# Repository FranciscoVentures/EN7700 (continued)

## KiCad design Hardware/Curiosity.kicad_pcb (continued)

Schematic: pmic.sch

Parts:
C79: 2.2uF; SM0402; Rating 25V/20%; Mfg PN GRM155R61E225ME15D; Digi-Key_PN 490-10457-1-ND
C80: 47uF; SM0603; Rating 6.3V/20%; Mfg PN GRM188R60J476ME15D; Digi-Key_PN 490-13247-1-ND
C81, C82, C83, C96, C99: 4.7uF; SM0402; Rating 10V/20%; Mfg PN ZRB15XR61A475ME01D; Digi-Key_PN 490-10984-1-ND
C84, C85, C86, C87, C88, C89, C95: 10uF; SM0402; Rating 10V/20%; Mfg PN CL05A106MP8NUB8; Digi-Key_PN 1276-6830-1-ND
C90, C91, C92, C93, C97, C103, C104: 1uF; SM0201; Rating 10V/20%; Mfg PN CL03A105MP3ZSNH; Digi-Key_PN 1276-6816-1-ND
C94, C102: 0.1uF; SM0201; Rating 10V/20%; Mfg PN GRM033R61A104ME15D; Digi-Key_PN 490-5405-1-ND
C98: 0.47uF; SM0201; Rating 6.3V/20%; Mfg PN GRM033R60J474ME90D; Digi-Key_PN 490-10410-1-ND
D3: LED RED; LED_0603; Rating 20mA/2V; Mfg PN LS Q976-NR-1; Digi-Key_PN 475-2512-1-ND
D4: LED BLUE; LED_0603; Rating 5mA/2.85V; Mfg PN LB Q39G-L2OO-35-1; Digi-Key_PN 475-2816-1-ND
L1, L2, L3: 1uH; SM0603; Rating 1.7A/20%/135mOhm; Mfg PN LPWI160808H1R0T; Digi-Key_PN F12082CT-ND
R43, R46, R49: 100K; R_0201_0603Metric; Rating 50mW/1%; Mfg PN CRCW0201100KJNED; Digi-Key_PN 541-100KAGCT-ND
R44: 0R; R_0201_0603Metric; Rating 0.05W; Mfg PN CRCW02010000Z0ED; Digi-Key_PN 541-0.0AGCT-ND
R52: 68R; R_0201_0603Metric; Rating 50mW/1%; Mfg PN CRCW020168R0FNED; Digi-Key_PN 541-CRCW020168R0FNEDCT-ND
R53: 100R; R_0201_0603Metric; Rating 50mW/1%; Mfg PN CRCW0201100RFNED; Digi-Key_PN 541-100ABCT-ND
U18: MC34PF1510A6EP; SOT1369-4; Mfg PN MC34PF1510A6EP; Digi-Key_PN 568-14653-1-ND

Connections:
/PMIC/LICELL: C94.1, U18.31 (LICELL)
/PMIC/VCORE: C103.1, U18.24 (VCORE)
/PMIC/VDIG: C104.1, U18.23 (VDIG)
/PMIC/VSYS: C80.1, C81.1, C82.1, C83.1, C90.1, C91.1, C92.1, R46.1, U18.11 (VLDO3IN), U18.14 (SW3IN), U18.17 (SW2IN), U18.20 (VLDO2IN), U18.26 (SW1IN), U18.28 (VLDO1IN), U18.35 (VSYS1), U18.36 (VSYS2)
DCDC_3V3: C88.1, C89.1, C102.1, D3.2 (A), L3.2, U18.4 (VDDIO), U18.15 (SW3FB); also elsewhere on the board
DDR_1V35: C86.1, C87.1, C93.1, L2.2, U18.16 (SW2FB), U18.22 (VINREFDDR); also elsewhere on the board
DDR_VREF: C97.1, U18.21 (VREFDDR); also elsewhere on the board
GND: C79.2, C80.2, C81.2, C82.2, C83.2, C84.2, C85.2, C86.2, C87.2, C88.2, C89.2, C90.2, C91.2, C92.2, C93.2, C94.2, C95.2, C96.2, C97.2, C98.2, C99.2, C102.2, C103.2, C104.2, R52.2, R53.2, U18.5 (VDDOTP), U18.7 (STANDBY), U18.32 (GND), U18.40 (GND), U18.41 (EP); also elsewhere on the board
GPS_3V3: D4.2 (A), R44.2; also elsewhere on the board
I2C1_SCL: U18.3 (SCL); also elsewhere on the board
I2C1_SDA: U18.2 (SDA); also elsewhere on the board
LDO1_1V8: C99.1, U18.29 (VLDO1); also elsewhere on the board
LDO2_3V3: C95.1, U18.19 (VLDO2); also elsewhere on the board
unnamed: C96.1, R44.1, U18.12 (VLDO3)
unnamed: D3.1 (K), R52.1
unnamed: D4.1 (K), R53.1
unnamed: L1.1, U18.25 (SW1LX)
unnamed: L2.1, U18.18 (SW2LX)
unnamed: L3.1, U18.13 (SW3LX)
unnamed: R46.2, U18.8 (ONKEY)
unnamed: R49.2, U18.6 (PWRON)
PMIC_WDI: R43.1, U18.1 (WDI); also elsewhere on the board
VDD_ARM_SOC_IN: C84.1, C85.1, L1.2, U18.27 (SW1FB); also elsewhere on the board
VSNVS_3V: C98.1, R43.2, R49.1, U18.30 (VSNVS); also elsewhere on the board
VSYS_5V: C79.1, U18.37 (VIN); also elsewhere on the board

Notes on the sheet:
EPAD: Tie to the inner and external ground planes through vias to allow effective thermal dissipation. [1] pg 8
400 mA
300 mA
1 A
10 mA
Power rails
ULZ: NXP MC34PF1510A6EP
3V3 PWR RED LED
GPS_PWR
GPS PWR BLUE LED
EMMC HS200
VSYS = 3.7V
VDD_ARM_SOC_IN = 1.275V

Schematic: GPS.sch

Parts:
C106: 47pF; 0603; Rating 50V/5%; Mfg PN C0603C470J5GACTU; Digi-Key_PN 399-1056-1-ND
C107: 4.7uF; SM0402; Rating 10V/20%; Mfg PN ZRB15XR61A475ME01D; Digi-Key_PN 490-10984-1-ND
C108: 0.1uF; SM0201; Rating 10V/20%; Mfg PN GRM033R61A104ME15D; Digi-Key_PN 490-5405-1-ND
C109, C110: 18pF; SM0201; Rating 50V/5%; Mfg PN GRM0335C1H180JA01D; Digi-Key_PN 490-6117-1-ND
FB1: BLM18PG121SN1D; 0603; Mfg PN BLM18PG121SN1D; Digi-Key_PN 490-1037-1-ND
J3: CONUFL001-SMD-T; U.FL_Molex_MCRF_73412-0110_Vertical; Mouser Part Number 712-CONUFL001-SMD-T
L4: 2.2uH; INDC2016X180N; Rating 0806; Mfg PN LQM2MPN2R2NG0L; Digi-Key_PN 490-7786-1-ND
R45, R47: 0R; R_0201_0603Metric; Rating 0.05W; Mfg PN CRCW02010000Z0ED; Digi-Key_PN 541-0.0AGCT-ND
R54, R57, R58: 10K; R_0201_0603Metric; Rating 50mW/1%; Mfg PN CRCW020110K0JNED; Digi-Key_PN 541-10KAGCT-ND
R56: 100R; 0603; Rating 100mW/1%; Mfg PN RC0603FR-07100RL; Digi-Key_PN 311-100HRCT-ND
U21: ZOE-M8Q; ZOEM8B; Mfg PN ZOE-M8Q-0-10; Digi-Key_PN 672-ZOE-M8Q-0-10CT-ND
U22: TPD1E10B06; X1SON-2; Mfg PN TPD1E10B06DPYR; Digi-Key_PN 296-30406-1-ND
Y3: 32.768kHz; CM7V-T1A; Mfg PN CM7V-T1A-32.768KHZ-12.5PF-20PPM-TB-QA; Digi-Key_PN 2195-CM7V-T1A-32.768KHZ-12.5PF-20PPM-TB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

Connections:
GND: C106.1, C107.2, C108.2, C109.2, C110.2, J3.2 (GND_1), U21.A1 (GND_1), U21.A3 (GND_2), U21.A5 (GND_3), U21.A7 (GND_4), U21.A8 (GND_5), U21.A9 (GND_6), U21.B9 (GND_7), U21.C7 (GND_8), U21.C9 (GND_9), U21.D6 (GND_10), U21.D9 (GND_11), U21.E7 (GND_12), U21.F7 (GND_13), U21.G3 (GND_14), U21.G6 (GND_15), U21.G7 (GND_16), U21.J3 (GND_17), U21.J9 (GND_18), U22.1; also elsewhere on the board
GPS_3V3: C108.1, R54.1, R56.2, R57.2, R58.1, U21.H9 (V_BCKP), U21.J1 (VCC_3), U21.J2 (VCC_4); also elsewhere on the board
GPS_ANT: FB1.1, J3.1 (SIG), U21.A4 (RF_IN), U22.2
GPS_PIO14: R54.2, U21.F6 (PIO14); also elsewhere on the board
GPS_RESET: R58.2, U21.J6 (RESET_N); also elsewhere on the board
GPS_SAFEBOOT_N: R57.1, U21.C4 (SAFEBOOT_N); also elsewhere on the board
GPS_UART_RX: U21.J5 (TXD/SPI_MISO); also elsewhere on the board
GPS_UART_TX: U21.J4 (RXD/SPI_MOSI); also elsewhere on the board
I2C2_SCL: R47.1; also elsewhere on the board
I2C2_SDA: R45.1; also elsewhere on the board
unnamed: C106.2, FB1.2, R56.1
unnamed: C107.1, L4.2, U21.G1 (VCC_1)
unnamed: C109.1, U21.J7 (RTC_I), Y3.2
unnamed: C110.1, U21.J8 (RTC_O), Y3.1
unnamed: L4.1, U21.H1 (VCC_2)
unnamed: R45.2, U21.A2 (SDA_/_SPI_CS_N)
unnamed: R47.2, U21.B1 (SCL_/_SPI_CLK)

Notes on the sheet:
GPS I2C Address 0X42

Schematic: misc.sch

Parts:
C111, C114, C119, C120, C125: 0.22uF; SM0201; Rating 6.3V/20%; Mfg PN GRM033R60J224ME15D; Digi-Key_PN 490-10407-1-ND
C112, C123: 1uF; SM0201; Rating 10V/20%; Mfg PN CL03A105MP3ZSNH; Digi-Key_PN 1276-6816-1-ND
C113, C115, C118, C121: 0.1uF; SM0201; Rating 10V/20%; Mfg PN GRM033R61A104ME15D; Digi-Key_PN 490-5405-1-ND
C116: 10nF; SM0201; Rating 6.3V/10%; Mfg PN GRM033R70J103KA01D; Digi-Key_PN 490-1262-1-ND
C117: 2.2nF; C_0402_1005Metric; Rating 50V/5%; Mfg PN GRM155R71H222JA01J; Digi-Key_PN 490-6359-1-ND
C122: 10uF; C_0402_1005Metric; Rating 10V/20%; Mfg PN CL05A106MP8NUB8; Digi-Key_PN 1276-6830-1-ND
C124: 10uF; SM0402; Rating 10V/20%; Mfg PN CL05A106MP8NUB8; Digi-Key_PN 1276-6830-1-ND
D6: LED GREEN; LED_0603; Rating 5mA/2.85V; Mfg PN LT Q39G-Q1OO-25-1; Digi-Key_PN 475-3442-1-ND
D7: LED BLUE; SM0603_LED; Rating 5mA/2.85V; Mfg PN LB Q39G-L2OO-35-1; Digi-Key_PN 475-2816-1-ND
LED1: LED ORANGE; LED_0603; Rating 20mA/2V; Mfg PN LO Q976-PS-25-0-20-R18; Digi-Key_PN 475-2486-1-ND
LED2: LED BLUE; LED_0603; Rating 5mA/2.85V; Mfg PN LB Q39G-L2OO-35-1; Digi-Key_PN 475-2816-1-ND
LED3: LED CYAN; LED_0603; Rating 5mA/2.8V; Mfg PN APT1608VRCXF/A-5MAV; Digi-Key_PN 754-2180-1-ND
LED4: LED GREEN; LED_0603; Rating 5mA/2.85V; Mfg PN LT Q39G-Q1OO-25-1; Digi-Key_PN 475-3442-1-ND
LED5: LED RED; LED_0603; Rating 20mA/2V; Mfg PN LS Q976-NR-1; Digi-Key_PN 475-2512-1-ND
R59, R60, R68, R69, R70: 100R; R_0201_0603Metric; Rating 50mW/1%; Mfg PN CRCW0201100RFNED; Digi-Key_PN 541-100ABCT-ND
R61, R64, R65: 4.7K; R_0201_0603Metric; Rating 50mW/1%; Mfg PN CRCW02014K70JNED; Digi-Key_PN 541-4.7KAGCT-ND
R62: 10R; R_0201_0603Metric; Rating 50mW/1%; Mfg PN CRCW020110R0FNED; Digi-Key_PN 541-10.0ABCT-ND
R63: 10K; R_0201_0603Metric; Rating 50mW/1%; Mfg PN CRCW020110K0JNED; Digi-Key_PN 541-10KAGCT-ND
R66: 100K; R_0201_0603Metric; Rating 50mW/1%; Mfg PN CRCW0201100KJNED; Digi-Key_PN 541-100KAGCT-ND
R67, R71: 68R; R_0201_0603Metric; Rating 50mW/1%; Mfg PN CRCW020168R0FNED; Digi-Key_PN 541-CRCW020168R0FNEDCT-ND
U2: i.MX6ULZ; SOT1534-2; Mfg PN MCIMX6Z0DVM09AB; Digi-Key_PN 568-14726-ND
U23: MPU-6050_NRND; QFN-24-1EP_4x4mm; Mfg PN MPU-6050; Digi-Key_PN 1428-1007-1-ND
U24: MS860702BA01-50; TE_MS860702BA01-50; Mfg PN MS860702BA01-50; Digi-Key_PN 223-1701-1-ND
U25: VEML6030-GS15; VISHAY_VEML6030_2X2X0.87; Mfg PN VEML6030-GS15; Digi-Key_PN VEML6030-GS15CT-ND
U26: MMC5883MA; PQFN50P300X300X100-16N; Mfg PN MMC5883MA; Digi-Key_PN 1267-1072-1-ND

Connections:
A71CH_RESET: U2.A16 (ENET2_TX_DATA1); also elsewhere on the board
Amb_sensor_INT: R63.1, U2.M17 (GPIO1_IO05), U25.3; also elsewhere on the board
DCDC_3V3: C111.1, C114.1, C115.1, C116.1, C119.1, C120.1, C123.1, C125.1, LED1.2 (A), LED2.2 (A), LED3.2 (A), LED4.2 (A), LED5.2 (A), R61.2, R62.2, R63.2, R64.1, R65.1, U2.C4 (NVCC_SD1), U2.F4 (NVCC_CSI), U2.F13 (NVCC_ENET), U2.J13 (NVCC_GPIO), U23.8 (VLOGIC), U23.13 (VDD), U24.1 (VDD), U26.2 (VDD), U26.13 (VDDIO); also elsewhere on the board
GND: C111.2, C112.2, C113.2, C114.2, C115.2, C116.2, C117.2, C118.2, C119.2, C120.2, C121.2, C122.2, C123.2, C124.2, C125.2, R66.2, U23.1 (CLKIN), U23.9 (AD0), U23.11 (FSYNC), U23.18 (GND), U24.3 (GND), U25.1, U26.9 (GND), U26.11 (GND); also elsewhere on the board
GPS_PIO14: U2.B1 (SD1_DATA2), U2.D16 (ENET2_RX_ER); also elsewhere on the board
GPS_RESET: U2.B2 (SD1_DATA1), U2.C16 (ENET2_RX_DATA1); also elsewhere on the board
GPS_SAFEBOOT_N: U2.C2 (SD1_CMD), U2.D17 (ENET2_TX_CLK); also elsewhere on the board
I2C1_SCL: R64.2, U2.L14 (GPIO1_IO02); also elsewhere on the board
I2C1_SDA: R65.2, U2.L17 (GPIO1_IO03); also elsewhere on the board
I2C2_SCL: U23.23 (SCL/SCLK), U24.8 (SCL), U25.5, U26.1 (SCL); also elsewhere on the board
I2C2_SDA: U23.24 (SDA), U24.7 (SDA), U25.2, U26.16 (SDA); also elsewhere on the board
ICS43434_SCK: U2.E1 (CSI_DATA03); also elsewhere on the board
ICS43434_SD: U2.D2 (CSI_DATA06); also elsewhere on the board
ICS43434_WS: U2.E2 (CSI_DATA02); also elsewhere on the board
LDO2_3V3: C112.1, C113.1, D6.2 (A), D7.2 (A), U2.L13 (VDDA_ADC_3P3), U2.M13 (ADC_VREFH); also elsewhere on the board
MPU6K_INT: R61.1, U2.L15 (GPIO1_IO01), U23.12 (INT); also elsewhere on the board
unnamed: C117.1, U23.20 (CPOUT)
unnamed: C118.1, U23.10 (REGOUT)
unnamed: C121.1, C122.1, R62.1, U25.4, U25.6
unnamed: C124.1, U26.10 (CAP)
unnamed: D6.1 (K), R59.1
unnamed: D7.1 (K), R60.1
unnamed: LED1.1 (K), R67.1
unnamed: LED2.1 (K), R68.1
unnamed: LED3.1 (K), R69.1
unnamed: LED4.1 (K), R70.1
unnamed: LED5.1 (K), R71.1
unnamed 179: R59.2, U2.E4 (CSI_DATA00); also elsewhere on the board
unnamed 180: R60.2, U2.E3 (CSI_DATA01); also elsewhere on the board
unnamed 181: U2.A2 (SD1_DATA3); also elsewhere on the board
unnamed 185: U2.A15 (ENET2_TX_DATA0); also elsewhere on the board
unnamed 186: U2.B3 (SD1_DATA0); also elsewhere on the board
unnamed 189: U2.B15 (ENET2_TX_EN); also elsewhere on the board
unnamed 190: U2.C1 (SD1_CLK); also elsewhere on the board
unnamed 193: U2.D1 (CSI_DATA07); also elsewhere on the board
unnamed 194: U2.D3 (CSI_DATA05); also elsewhere on the board
unnamed 195: U2.D4 (CSI_DATA04); also elsewhere on the board
unnamed 198: U2.D15 (ENET1_RX_ER); also elsewhere on the board
unnamed 199: U2.E5 (CSI_PIXCLK); also elsewhere on the board
unnamed 202: U2.E14 (ENET1_TX_DATA1); also elsewhere on the board
unnamed 203: U2.E15 (ENET1_TX_DATA0); also elsewhere on the board
unnamed 204: U2.E16 (ENET1_RX_EN); also elsewhere on the board
unnamed 205: U2.E17 (ENET1_RX_DATA1); also elsewhere on the board
unnamed 207: U2.F2 (CSI_VSYNC); also elsewhere on the board
unnamed 208: U2.F3 (CSI_HSYNC); also elsewhere on the board
unnamed 209: U2.F5 (CSI_MCLK); also elsewhere on the board
unnamed 210: U2.F14 (ENET1_TX_CLK); also elsewhere on the board
unnamed 211: U2.F16 (ENET1_RX_DATA0); also elsewhere on the board
PMIC_WDI: U2.F15 (ENET1_TX_EN); also elsewhere on the board
SE1_LED: R67.2, U2.M15 (GPIO1_IO09); also elsewhere on the board
SE2_LED: R68.2, U2.N17 (GPIO1_IO08); also elsewhere on the board
SE3_LED: R69.2, U2.L16 (GPIO1_IO07); also elsewhere on the board
SE4_LED: R70.2, U2.K17 (GPIO1_IO06); also elsewhere on the board
SE5_LED: R71.2, U2.M16 (GPIO1_IO04); also elsewhere on the board
SLS32A_RESET: U2.C17 (ENET2_RX_DATA0); also elsewhere on the board
USB1_INT_B: U2.K13 (GPIO1_IO00); also elsewhere on the board
eCompass_INT: R66.1, U2.B17 (ENET2_RX_EN), U26.15 (INT); also elsewhere on the board

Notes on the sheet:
ADC_VREFH: tied to VDDA_ADC_3P3 [1] pg 18
VDDA_ADC_3P3 must be powered even if the ADC is not used. [1] pg 18
I2C1_SCL [ALT0]
I2C1_SDA [ALT0]
GPIO1_IO9 [ALT5]
GPIO1_IO6 [ALT5]
GPIO1_IO4 [ALT5]
I2C1 ADDRESSES (8bit address / 7 bit address) 0x10 / 0x08: PMIC (400 kHz) 0xC0 / 0x60: ATECC608A Microchip SECURE ELEMENT (1 MHz) 0x92 / 0x49: A71CH NXP SECURE ELEMENT (400 kHz) 0xC2 / 0x61: TUSB320 USB1 (Type-C plug) (400 kHz) 0x30 / 0x : SLS32AIA010MH OPTIGA SECURE ELEMENT (400kHz) 0x50 / 0x : A1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
GPIO1_IO0 [ALT5]
ENET1_TX_EN (ULZ: KPP_COL2) -> WDOG2_WDOG_RST_B_DEB [ALT8]
CSI_DATA00 (ULZ: SD2_DATA0) -> GPIO4_IO21 [ALT5]
CSI_DATA01 (ULZ: SD2_DATA1) -> GPIO4_IO22 [ALT5]
ULZ: VDD_HIGH_IN
Secure Elements LEDS
Pressure, Humidity & Temp Sensors
I2C Adress: Pressure & Tempreature: 0x76 Relative Humidity: 0x40
High Accuracy Ambient Light Sensor
I2C Adress: 0x48
GPIO1_IO5 [ALT5]-Ambient Sensor Interrupt
GPIO1_IO7 [ALT5]
GPIO1_IO8 [ALT5]
I2C Adress: 0x68
GPIO1_IO1 [ALT5]
Accelerometer, Gyroscope, 6 Axis Sensor
RX_SYNC -> CSI_DATA02 -> GPIO4_IO23
RX_BCLK -> CSI_DATA03 -> GPIO4_IO24
RX_DATA -> CSI_DATA06 -> GPIO4_IO27
GPIO2_IO8
GPIO2_IO9
GPIO2_IO15
e-Compass
I2C Adress: 0x30
GPIO2_IO14
I2C2 ADDRESSES (8bit address / 7 bit address) 0x76 / 0xXX: Pressure & Tempreature (400KHz) 0x40 / 0xXX: Relative Humidity (400KHz) 0x48 / 0xXX: Ambient Light Sensor (400KHz) 0x68 / 0xXX: Acc Gyro 6 Axis Sensor (400KHz) 0x30 / 0xXX: eCompass (400KHz) 0x42 / 0x21: GPS ZOE-M8Q-0-10 (400 kHz) 0x52 / 0x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
GPIO2_IO10

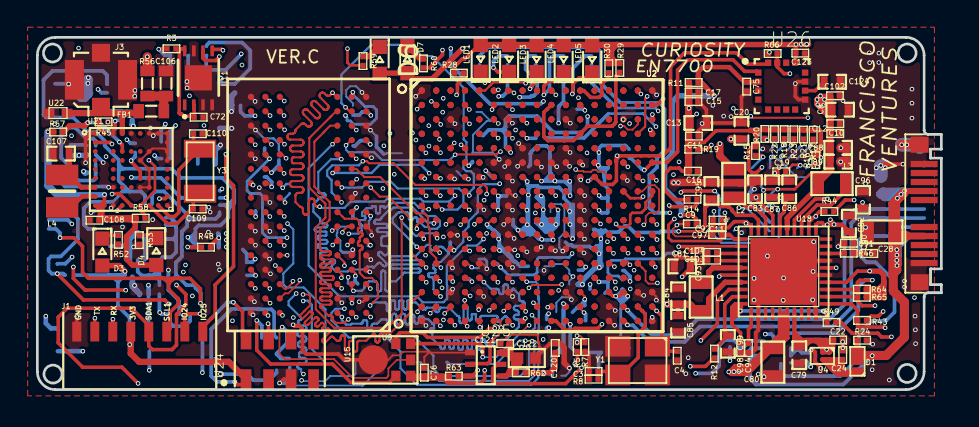
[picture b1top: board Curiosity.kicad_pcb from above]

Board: 8 copper layers, 50.2 x 19.6 mm, 246 parts (0 on the bottom side), 257 nets.

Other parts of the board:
U2#2: i.MX6ULZ; SOT1534-2

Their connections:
/Boot/BT_CFG1[0]: U2#2.B9; also elsewhere on the board
/Boot/BT_CFG1[1]: U2#2.A9; also elsewhere on the board
/Boot/BT_CFG1[2]: U2#2.E10; also elsewhere on the board
/Boot/BT_CFG1[3]: U2#2.D10; also elsewhere on the board
/Boot/BT_CFG1[4]: U2#2.C10; also elsewhere on the board
/Boot/BT_CFG1[5]: U2#2.B10, U2#2.D12; also elsewhere on the board
/Boot/BT_CFG1[6]: U2#2.A10; also elsewhere on the board
/Boot/BT_CFG1[7]: U2#2.D11; also elsewhere on the board
/Boot/BT_CFG2[0]: U2#2.B11; also elsewhere on the board
/Boot/BT_CFG2[1]: U2#2.A11; also elsewhere on the board
/Boot/BT_CFG2[2]: U2#2.E12; also elsewhere on the board
/Boot/BT_CFG2[4]: U2#2.C12; also elsewhere on the board
/Boot/BT_CFG2[5]: U2#2.B12; also elsewhere on the board
/Boot/BT_CFG2[6]: U2#2.A12; also elsewhere on the board
/Boot/BT_CFG2[7]: U2#2.D13; also elsewhere on the board
/Boot/BT_CFG4[0]: U2#2.C13; also elsewhere on the board
/Boot/BT_CFG4[1]: U2#2.B13; also elsewhere on the board
/Boot/BT_CFG4[2]: U2#2.A13; also elsewhere on the board
/Boot/BT_CFG4[3]: U2#2.D14; also elsewhere on the board
/Boot/BT_CFG4[4]: U2#2.C14; also elsewhere on the board
/Boot/BT_CFG4[5]: U2#2.B14; also elsewhere on the board
/Boot/BT_CFG4[6]: U2#2.A14; also elsewhere on the board
/Boot/BT_CFG4[7]: U2#2.B16; also elsewhere on the board
/Crystals/BOOT_MODE0: U2#2.T10; also elsewhere on the board
/Crystals/BOOT_MODE1: U2#2.U10; also elsewhere on the board
/Crystals/JTAG_MOD: U2#2.P15; also elsewhere on the board
/Crystals/JTAG_TCK: U2#2.M14; also elsewhere on the board
/Crystals/JTAG_TDI: U2#2.N16; also elsewhere on the board
/Crystals/JTAG_TDO: U2#2.N15; also elsewhere on the board
/Crystals/JTAG_TMS: U2#2.P14; also elsewhere on the board
/Crystals/JTAG_nSRST: U2#2.P8; also elsewhere on the board
/Crystals/JTAG_nTRST: U2#2.N14; also elsewhere on the board
/Crystals/RTC_XTALI: U2#2.T11; also elsewhere on the board
/Crystals/RTC_XTALO: U2#2.U11; also elsewhere on the board
/Crystals/XTALI: U2#2.T16; also elsewhere on the board
/Crystals/XTALO: U2#2.T17; also elsewhere on the board
/DDR/DRAM_A0: U2#2.L5; also elsewhere on the board
/DDR/DRAM_A1: U2#2.H2; also elsewhere on the board
/DDR/DRAM_A2: U2#2.K1; also elsewhere on the board
/DDR/DRAM_A3: U2#2.M2; also elsewhere on the board
/DDR/DRAM_A4: U2#2.K4; also elsewhere on the board
/DDR/DRAM_A5: U2#2.L1; also elsewhere on the board
/DDR/DRAM_A6: U2#2.G2; also elsewhere on the board
/DDR/DRAM_A7: U2#2.H4; also elsewhere on the board
/DDR/DRAM_A8: U2#2.J4; also elsewhere on the board
/DDR/DRAM_A9: U2#2.L2; also elsewhere on the board
/DDR/DRAM_A10: U2#2.M4; also elsewhere on the board
/DDR/DRAM_A11: U2#2.K3; also elsewhere on the board
/DDR/DRAM_A12: U2#2.L4; also elsewhere on the board
/DDR/DRAM_A13: U2#2.H3; also elsewhere on the board
/DDR/DRAM_A14: U2#2.G1; also elsewhere on the board
/DDR/DRAM_A15: U2#2.K5; also elsewhere on the board
/DDR/DRAM_CAS_B: U2#2.J2; also elsewhere on the board
/DDR/DRAM_CS0_B: U2#2.N2; also elsewhere on the board
/DDR/DRAM_D0: U2#2.T4; also elsewhere on the board
/DDR/DRAM_D1: U2#2.U6; also elsewhere on the board
/DDR/DRAM_D2: U2#2.T6; also elsewhere on the board
/DDR/DRAM_D3: U2#2.U7; also elsewhere on the board
/DDR/DRAM_D4: U2#2.U8; also elsewhere on the board
/DDR/DRAM_D5: U2#2.T8; also elsewhere on the board
/DDR/DRAM_D6: U2#2.T5; also elsewhere on the board
/DDR/DRAM_D7: U2#2.U4; also elsewhere on the board
/DDR/DRAM_D8: U2#2.U2; also elsewhere on the board
/DDR/DRAM_D9: U2#2.U3; also elsewhere on the board
/DDR/DRAM_D10: U2#2.U5; also elsewhere on the board
/DDR/DRAM_D11: U2#2.R4; also elsewhere on the board
/DDR/DRAM_D12: U2#2.P5; also elsewhere on the board
/DDR/DRAM_D13: U2#2.P3; also elsewhere on the board
/DDR/DRAM_D14: U2#2.R2; also elsewhere on the board
/DDR/DRAM_D15: U2#2.R1; also elsewhere on the board
/DDR/DRAM_DQM0: U2#2.T7; also elsewhere on the board
/DDR/DRAM_DQM1: U2#2.T3; also elsewhere on the board
/DDR/DRAM_RAS_B: U2#2.M5; also elsewhere on the board
/DDR/DRAM_RESET_B: U2#2.G4; also elsewhere on the board
/DDR/DRAM_SDBA0: U2#2.M1; also elsewhere on the board
/DDR/DRAM_SDBA1: U2#2.H1; also elsewhere on the board
/DDR/DRAM_SDBA2: U2#2.K2; also elsewhere on the board
/DDR/DRAM_SDCKE0: U2#2.M3; also elsewhere on the board
/DDR/DRAM_SDCLK0_N: U2#2.P2; also elsewhere on the board
/DDR/DRAM_SDCLK0_P: U2#2.P1; also elsewhere on the board
/DDR/DRAM_SDODT0: U2#2.N1; also elsewhere on the board
/DDR/DRAM_SDQS0_N: U2#2.P7; also elsewhere on the board
/DDR/DRAM_SDQS0_P: U2#2.P6; also elsewhere on the board
/DDR/DRAM_SDQS1_N: U2#2.T2; also elsewhere on the board
/DDR/DRAM_SDQS1_P: U2#2.T1; also elsewhere on the board
/DDR/DRAM_WE_B: U2#2.J1; also elsewhere on the board
/DDR/DRAM_ZQPAD: U2#2.N4; also elsewhere on the board
/Power/NVCC_PLL_OUT: U2#2.P13; also elsewhere on the board
/Power/VDD_ARM_CAP: U2#2.G9, U2#2.G10, U2#2.G11, U2#2.H11; also elsewhere on the board
/Power/VDD_SNVS_CAP: U2#2.N12; also elsewhere on the board
/Power/VDD_SOC_CAP: U2#2.G8, U2#2.H8, U2#2.J8, U2#2.J11, U2#2.K8, U2#2.K11, U2#2.L8, U2#2.L9, U2#2.L10, U2#2.L11; also elsewhere on the board
/USB/USB1_DN: U2#2.T15; also elsewhere on the board
/USB/USB1_DP: U2#2.U15; also elsewhere on the board
/USB/VDD_USB_CAP: U2#2.R12; also elsewhere on the board
/eMMC/SD2_CLK_R: U2#2.D8; also elsewhere on the board
/eMMC/SD2_CMD: U2#2.C8; also elsewhere on the board
/eMMC/SD2_DATA0: U2#2.D7; also elsewhere on the board
/eMMC/SD2_DATA1: U2#2.B7; also elsewhere on the board
/eMMC/SD2_DATA2: U2#2.A7; also elsewhere on the board
/eMMC/SD2_DATA3: U2#2.D6; also elsewhere on the board
/eMMC/SD2_DATA4: U2#2.C6; also elsewhere on the board
/eMMC/SD2_DATA5: U2#2.B6; also elsewhere on the board
/eMMC/SD2_DATA6: U2#2.A6; also elsewhere on the board
/eMMC/SD2_DATA7: U2#2.A5; also elsewhere on the board
/eMMC/SD2_RESET_B: U2#2.B4; also elsewhere on the board
A71CH_RESET: U2#2.A16; also elsewhere on the board
Amb_sensor_INT: U2#2.M17; also elsewhere on the board
DCDC_3V3: U2#2.C4, U2#2.E13, U2#2.F4, U2#2.F13, U2#2.H13, U2#2.J13; also elsewhere on the board
DDR_1V35: U2#2.G6, U2#2.H6, U2#2.J6, U2#2.K6, U2#2.L6, U2#2.M6; also elsewhere on the board
DDR_VREF: U2#2.P4; also elsewhere on the board
GND: U2#2.A1, U2#2.A17, U2#2.C3, U2#2.C7, U2#2.C11, U2#2.C15, U2#2.E8, U2#2.E11, U2#2.F6, U2#2.F7, U2#2.F8, U2#2.F9, U2#2.F10, U2#2.F11, U2#2.F12, U2#2.G3, U2#2.G5, U2#2.G7, U2#2.G12, U2#2.G15, U2#2.H7, U2#2.H12, U2#2.J5, U2#2.J7, U2#2.J12, U2#2.K7, U2#2.K12, U2#2.L3, U2#2.L7, U2#2.L12, U2#2.M7, U2#2.M8, U2#2.M9, U2#2.M10, U2#2.M11, U2#2.M12, U2#2.N3, U2#2.N5, U2#2.N7, U2#2.R3, U2#2.R5, U2#2.R7, U2#2.R11, U2#2.R16, U2#2.R17, U2#2.T14, U2#2.U1, U2#2.U14, U2#2.U17; also elsewhere on the board
GPIO1_IO25: U2#2.H15; also elsewhere on the board
GPIO1_IO27: U2#2.G14; also elsewhere on the board
GPS_PIO14: U2#2.B1, U2#2.D16; also elsewhere on the board
GPS_RESET: U2#2.B2, U2#2.C16; also elsewhere on the board
GPS_SAFEBOOT_N: U2#2.C2, U2#2.D17; also elsewhere on the board
GPS_UART_RX: U2#2.H16; also elsewhere on the board
GPS_UART_TX: U2#2.H17; also elsewhere on the board
I2C1_SCL: U2#2.L14; also elsewhere on the board
I2C1_SDA: U2#2.L17; also elsewhere on the board
I2C2_SCL: U2#2.F17; also elsewhere on the board
I2C2_SDA: U2#2.G13; also elsewhere on the board
ICS43434_SCK: U2#2.E1; also elsewhere on the board
ICS43434_SD: U2#2.D2; also elsewhere on the board
ICS43434_WS: U2#2.E2; also elsewhere on the board
LDO2_3V3: U2#2.L13, U2#2.M13, U2#2.N13, U2#2.P12; also elsewhere on the board
MPU6K_INT: U2#2.L15; also elsewhere on the board
NVCC_NAND: U2#2.E7; also elsewhere on the board
unnamed 179: U2#2.E4; also elsewhere on the board
unnamed 180: U2#2.E3; also elsewhere on the board
unnamed 181: U2#2.A2; also elsewhere on the board
unnamed 182: U2#2.A3; also elsewhere on the board
unnamed 183: U2#2.A4; also elsewhere on the board
unnamed 184: U2#2.A8; also elsewhere on the board
unnamed 185: U2#2.A15; also elsewhere on the board
unnamed 186: U2#2.B3; also elsewhere on the board
unnamed 187: U2#2.B5; also elsewhere on the board
unnamed 188: U2#2.B8; also elsewhere on the board
unnamed 189: U2#2.B15; also elsewhere on the board
unnamed 190: U2#2.C1; also elsewhere on the board
unnamed 191: U2#2.C5; also elsewhere on the board
unnamed 192: U2#2.C9; also elsewhere on the board
unnamed 193: U2#2.D1; also elsewhere on the board
unnamed 194: U2#2.D3; also elsewhere on the board
unnamed 195: U2#2.D4; also elsewhere on the board
unnamed 196: U2#2.D5; also elsewhere on the board
unnamed 197: U2#2.D9; also elsewhere on the board
unnamed 198: U2#2.D15; also elsewhere on the board
unnamed 199: U2#2.E5; also elsewhere on the board
unnamed 200: U2#2.E6; also elsewhere on the board
unnamed 201: U2#2.E9; also elsewhere on the board
unnamed 202: U2#2.E14; also elsewhere on the board
unnamed 203: U2#2.E15; also elsewhere on the board
unnamed 204: U2#2.E16; also elsewhere on the board
unnamed 205: U2#2.E17; also elsewhere on the board
unnamed 206: U2#2.F1; also elsewhere on the board
unnamed 207: U2#2.F2; also elsewhere on the board
unnamed 208: U2#2.F3; also elsewhere on the board
unnamed 209: U2#2.F5; also elsewhere on the board
unnamed 210: U2#2.F14; also elsewhere on the board
unnamed 211: U2#2.F16; also elsewhere on the board
unnamed 212: U2#2.H5; also elsewhere on the board
unnamed 213: U2#2.H14; also elsewhere on the board
unnamed 214: U2#2.J3; also elsewhere on the board
unnamed 215: U2#2.J14; also elsewhere on the board
unnamed 216: U2#2.J15; also elsewhere on the board
unnamed 217: U2#2.J16; also elsewhere on the board
unnamed 218: U2#2.J17; also elsewhere on the board
unnamed 219: U2#2.K14; also elsewhere on the board
unnamed 220: U2#2.K15; also elsewhere on the board
unnamed 221: U2#2.K16; also elsewhere on the board
unnamed 222: U2#2.N8; also elsewhere on the board
unnamed 223: U2#2.N9; also elsewhere on the board
unnamed 224: U2#2.N10; also elsewhere on the board
unnamed 225: U2#2.N11; also elsewhere on the board
unnamed 226: U2#2.P9; also elsewhere on the board
unnamed 227: U2#2.P10; also elsewhere on the board
unnamed 228: U2#2.P11; also elsewhere on the board
unnamed 229: U2#2.P16; also elsewhere on the board
unnamed 230: U2#2.P17; also elsewhere on the board
unnamed 231: U2#2.R6; also elsewhere on the board
unnamed 232: U2#2.R8; also elsewhere on the board
unnamed 233: U2#2.R9; also elsewhere on the board
unnamed 234: U2#2.R10; also elsewhere on the board
unnamed 235: U2#2.R13; also elsewhere on the board
unnamed 236: U2#2.T9; also elsewhere on the board
unnamed 237: U2#2.T13; also elsewhere on the board
unnamed 238: U2#2.U9; also elsewhere on the board
unnamed 239: U2#2.U12; also elsewhere on the board
unnamed 240: U2#2.U13; also elsewhere on the board
unnamed 241: U2#2.U16; also elsewhere on the board
PMIC_WDI: U2#2.F15; also elsewhere on the board
SE1_LED: U2#2.M15; also elsewhere on the board
SE2_LED: U2#2.N17; also elsewhere on the board
SE3_LED: U2#2.L16; also elsewhere on the board
SE4_LED: U2#2.K17; also elsewhere on the board
SE5_LED: U2#2.M16; also elsewhere on the board
SLS32A_RESET: U2#2.C17; also elsewhere on the board
UART4_RX: U2#2.G16; also elsewhere on the board
UART4_TX: U2#2.G17; also elsewhere on the board
USB1_INT_B: U2#2.K13; also elsewhere on the board
VDD_ARM_SOC_IN: U2#2.H9, U2#2.H10, U2#2.J9, U2#2.J10, U2#2.K9, U2#2.K10; also elsewhere on the board
VDD_HIGH_CAP: U2#2.N6, U2#2.R14, U2#2.R15; also elsewhere on the board
VSYS_5V: U2#2.T12; also elsewhere on the board
eCompass_INT: U2#2.B17; also elsewhere on the board

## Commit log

2021-01-12 changes the copyright
2021-01-12 change the copyright
2021-01-12 modified: .DS_Store
2021-01-12 modified readme
